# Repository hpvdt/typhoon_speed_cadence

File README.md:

# Typhoon Speed and Cadence

This is the amazing repository for the amazing Speed and Cadance team.
This embedded system uses an STM32 and a hall effect setup to accurately calculate the speed of the bike in real time, displaying the information to an OLED
HOE: Oliver Cai, Juston Lo
Lead: Daniel Dot
Members: Luca M, Rena, Noah, Iris

MEMBERS ADD YOUR LAST NAMES PLEASE I DONT KNOW THEM :(

## Hardware Setup

We must all operate on the same main version of KiCad, 9.0.
Ensure you are always working on the project file, never open the files standalone.

## Firmware Setup

### THIS PART IS VERY IMPORTANT PLEASE READ

We must all operate on the same versions, if we do not then stuff will break. We are currently using:
- STM32CubeIDE 2.0.0
- STM32CubeMX 6.16.0

You must download both to program as the IDE is used oto program while the CubeMX is for the .ioc file to configure the board pinout.

When writing code in the main.c, main.h, or any program where code is overwritten from the .ioc save, PLEASE ENSURE YOU ARE WRITING IN A USER CODE BLOCK, or else your code will be removed.

The main code is found in main.c in the src folder, and whenever working on the code always work in the project folder, dont open the file standalone. 
The logic for the code is commented in code, and any changes MUST also be commented for others to work simultaneously on it.

If there are any questions about the project, message me on disc dot2944, or email daniel.dot@mail.utoronto.ca

## Organization

Pretty self-explanitory, put hardware related files into the `hardware` folder, firmware in the `firmware` folder. Other folders can be added as needed: for example a `media` folder is handy for storing pictures related to a project which can be used in documentation.

## Conventions

Partly for consistency, partly for functionality; please follow the following conventions:

- Try to keep folder names to single words and all lowercase
- Use underscores to separate words in names (e.g. `board_rev1`). **DO NOT USE SPACES! ESPECIALLY FOR FOLDERS CONTAINING CODE!** Spaces in file paths may cause issues in compilers and such so best to avoid them entirely.

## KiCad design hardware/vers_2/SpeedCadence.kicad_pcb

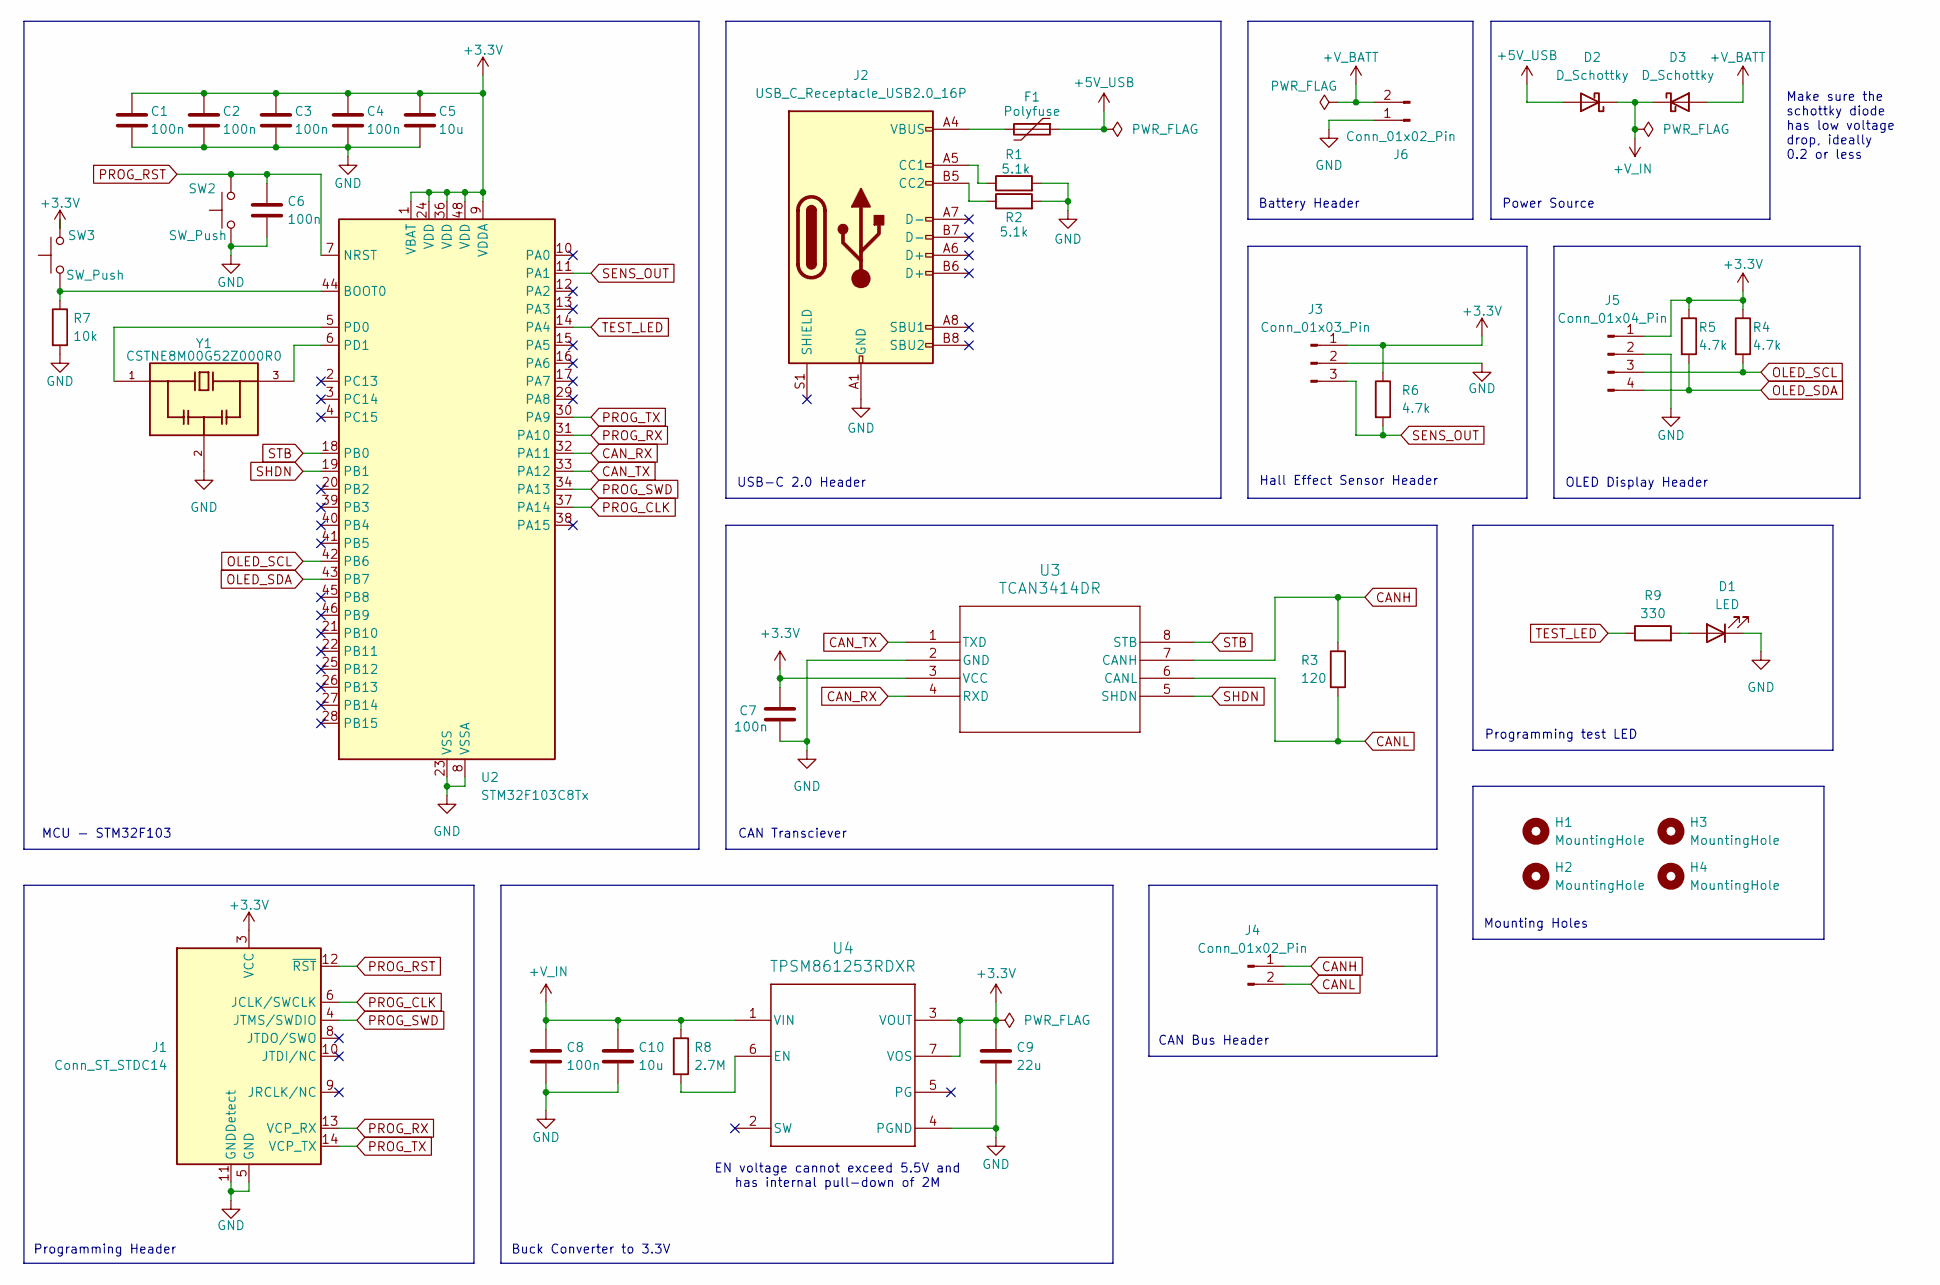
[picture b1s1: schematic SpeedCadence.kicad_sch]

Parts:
C1, C2, C3, C4, C6, C7, C8: 100n; C_0805_2012Metric; Manufacturer Part Number CC0805KRX7R9BB104
C5, C10: 10u; C_0805_2012Metric; Manufacturer Part Number GRM21BR71A106KA73K
C9: 22u; C_0805_2012Metric; Manufacturer Part Number GRM21BZ71A226ME15L
D1: LED; LED_0805_2012Metric; Manufacturer Part Number 5975906507F
D2, D3: D_Schottky; D_SOD-123; Manufacturer Part Number 1N5819HW-7-F
F1: Polyfuse; Fuse_1206_3216Metric; Manufacturer Part Number 0ZCJ0020FF2E
H1, H2, H3, H4: MountingHole; MountingHole_2.2mm_M2
J1: Conn_ST_STDC14; PinHeader_2x07_P1.27mm_Vertical_SMD; Manufacturer Part Number FTSH-107-01-L-DV-K-A
J2: USB_C_Receptacle_USB2.0_16P; USB_C_Receptacle_JAE_DX07S016JA1R1500; Manufacturer Part Number DX07S016JA3R1500
J3: Conn_01x03_Pin; JST_XH_B3B-XH-A_1x03_P2.50mm_Vertical; Manufacturer Part Number B3B-XH-A(LF)(SN)
J4, J6: Conn_01x02_Pin; JST_XH_B2B-XH-A_1x02_P2.50mm_Vertical; Manufacturer Part Number B2B-XH-A-BK(LF)(SN)
J5: Conn_01x04_Pin; JST_XH_B4B-XH-A_1x04_P2.50mm_Vertical; Manufacturer Part Number B4B-XH-A(LF)(SN)
R1, R2: 5.1k; R_0805_2012Metric; Manufacturer Part Number RC0805JR-075K1L
R3: 120; R_0805_2012Metric; Manufacturer Part Number P0603Y60R0BBT
R4, R5, R6: 4.7k; R_0805_2012Metric
R7: 10k; R_0805_2012Metric
R8: 2.7M; R_0805_2012Metric
R9: 330; R_0805_2012Metric
SW2, SW3: SW_Push; SW_SPST_SKQG_WithStem
U2: STM32F103C8Tx; LQFP-48_7x7mm_P0.5mm
U3: TCAN3414DR; SOIC-8_3.9x4.9mm_P1.27mm
U4: TPSM861253RDXR; VREG_TPSM861253RDXR
Y1: CSTNE8M00G52Z000R0; OSC_CSTNE8M00G52Z000R0; PARTREV JGC42-8858A

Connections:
+3.3V: C1.2, C2.2, C3.2, C4.2, C5.1, C7.1, C9.1, J1.3 (VCC), J3.1, J5.1, R4.1, R5.1, R6.1, SW3.2, U2.1 (VBAT), U2.9 (VDDA), U2.24 (VDD), U2.36 (VDD), U2.48 (VDD), U3.3 (VCC), U4.3 (VOUT), U4.7 (VOS), U4.14, U4.15, U4.16, U4.17, U4.18, U4.19
+5V_USB: D2.2 (A), F1.1
+V_BATT: D3.2 (A), J6.2
+V_IN: C8.1, C10.1, D2.1 (K), D3.1 (K), R8.1, U4.1 (VIN)
CANH: J4.1, R3.1, U3.7 (CANH)
CANL: J4.2, R3.2, U3.6 (CANL)
CAN_RX: U2.32 (PA11), U3.4 (RXD)
CAN_TX: U2.33 (PA12), U3.1 (TXD)
GND: C1.1, C2.1, C3.1, C4.1, C5.2, C6.2, C7.2, C8.2, C9.2, C10.2, D1.1 (K), J1.5 (GND), J1.7 (GND), J1.11 (GNDDetect), J2.A1 (GND), J2.A12 (GND), J2.B1 (GND), J2.B12 (GND), J3.2, J5.2, J6.1, R1.2, R2.2, R7.2, SW2.1, U2.8 (VSSA), U2.23 (VSS), U2.35 (VSS), U2.47 (VSS), U3.2 (GND), U4.4 (PGND), Y1.2
unnamed: D1.2 (A), R9.2
unnamed: F1.2, J2.A4 (VBUS), J2.A9 (VBUS), J2.B4 (VBUS), J2.B9 (VBUS)
unnamed: J2.A5 (CC1), R1.1
unnamed: J2.B5 (CC2), R2.1
unnamed: R7.1, SW3.1, U2.44 (BOOT0)
unnamed: U2.5 (PD0), Y1.1
unnamed: U2.6 (PD1), Y1.3
unnamed: R8.2, U4.6 (EN)
OLED_SCL: J5.3, R4.2, U2.42 (PB6)
OLED_SDA: J5.4, R5.2, U2.43 (PB7)
PROG_CLK: J1.6 (JCLK/SWCLK), U2.37 (PA14)
PROG_RST: C6.1, J1.12 (~RST), SW2.2, U2.7 (NRST)
PROG_RX: J1.13 (VCP_RX), U2.31 (PA10)
PROG_SWD: J1.4 (JTMS/SWDIO), U2.34 (PA13)
PROG_TX: J1.14 (VCP_TX), U2.30 (PA9)
SENS_OUT: J3.3, R6.2, U2.11 (PA1)
SHDN: U2.19 (PB1), U3.5 (SHDN)
STB: U2.18 (PB0), U3.8 (STB)
TEST_LED: R9.1, U2.14 (PA4)

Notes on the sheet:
Mounting Holes
CAN Transciever
MCU - STM32F103
CAN Bus Header
Battery Header
USB-C 2.0 Header
Buck Converter to 3.3V
Power Source
Hall Effect Sensor Header
EN voltage cannot exceed 5.5V and has internal pull-down of 2M
OLED Display Header
Programming Header
Programming test LED
Make sure the schottky diode has low voltage drop, ideally 0.2 or less

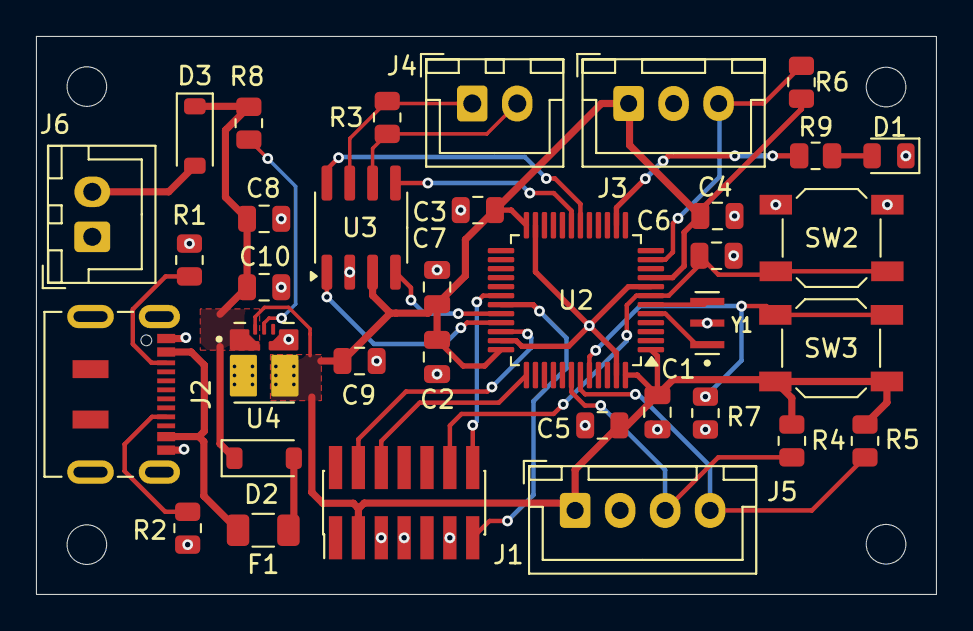
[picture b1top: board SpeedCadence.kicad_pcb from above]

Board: 2 copper layers, 50.0 x 31.0 mm, 39 parts (0 on the bottom side), 28 nets.

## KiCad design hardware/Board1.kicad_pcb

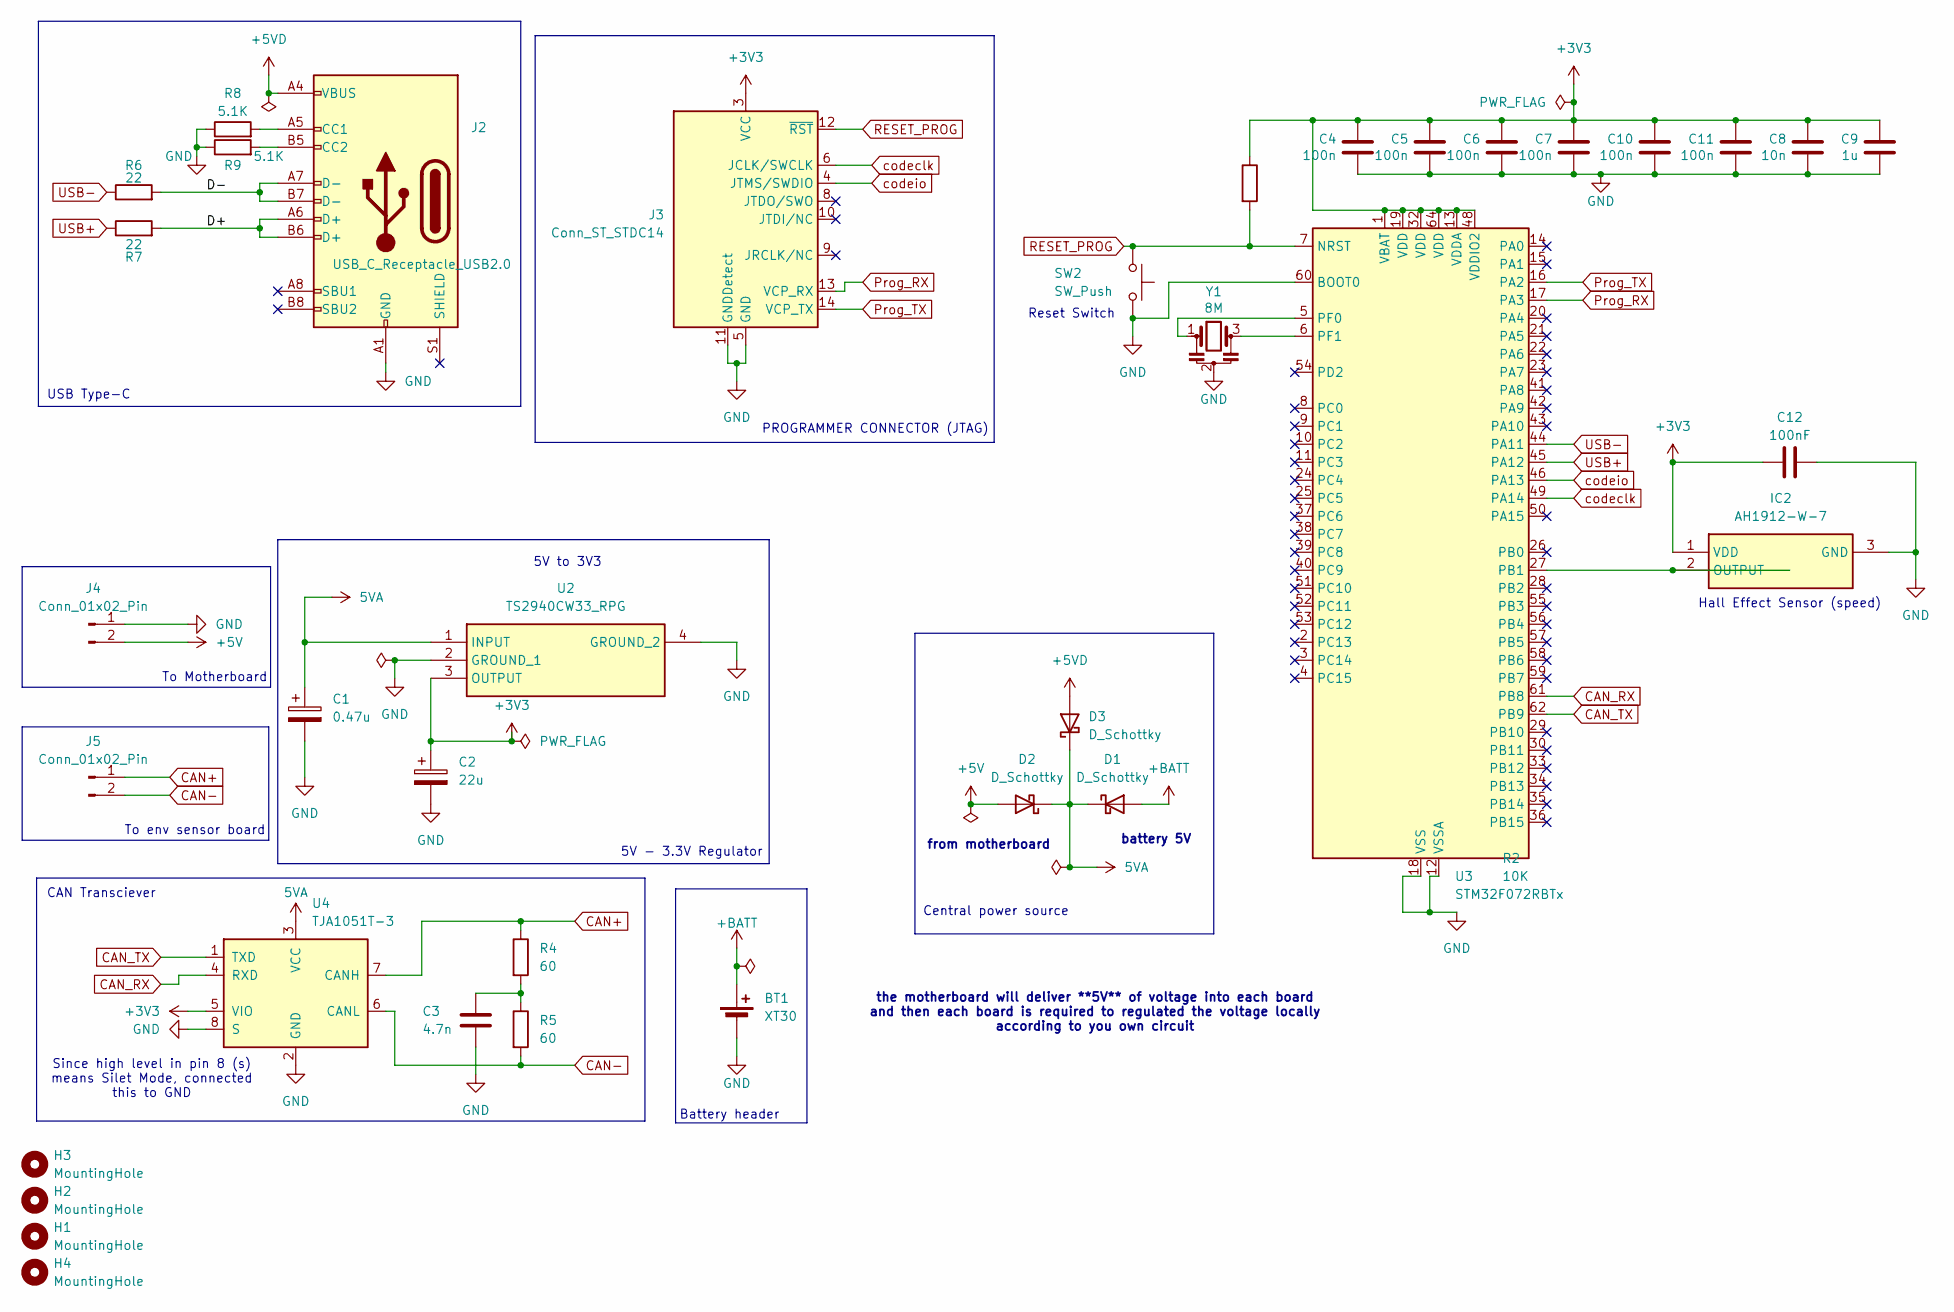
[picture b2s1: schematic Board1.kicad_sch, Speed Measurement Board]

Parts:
BT1: XT30; AMASS_XT30PW-M_1x02_P2.50mm_Horizontal
C1: 0.47u; C_1206_3216Metric
C2: 22u; C_1206_3216Metric
C3: 4.7n; C_0603_1608Metric
C4, C5, C6, C7, C10, C11: 100n; C_0603_1608Metric
C8: 10n; C_0603_1608Metric
C9: 1u; C_0603_1608Metric
C12: 100nF; C_0603_1608Metric
D1, D2, D3: D_Schottky; D_SOD-123
H1, H2, H3, H4: MountingHole; MountingHole_3.2mm_M3_ISO14580
IC2: AH1912-W-7; SC-59; Mouser Part Number 621-AH1912-W-7
J2: USB_C_Receptacle_USB2.0; USB_C_Receptacle_HRO_TYPE-C-31-M-12
J3: Conn_ST_STDC14; PinHeader_2x07_P1.27mm_Vertical_SMD
J4, J5: Conn_01x02_Pin; JST_EH_S2B-EH_1x02_P2.50mm_Horizontal
R2: 10K; R_0603_1608Metric
R4, R5: 60; R_0603_1608Metric
R6, R7: 22; R_0603_1608Metric
R8, R9: 5.1K; R_0603_1608Metric
SW2: SW_Push; SW_SPST_SKQG_WithStem
U2: TS2940CW33_RPG; SOT-223-3_TabPin2; Mouser Part Number 821-TS2940CW33RPG
U3: STM32F072RBTx; LQFP-64_10x10mm_P0.5mm
U4: TJA1051T-3; SOIC-8_3.9x4.9mm_P1.27mm
Y1: 8M; Resonator_SMD_Murata_CSTxExxV-3Pin_3.0x1.1mm

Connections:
5VA: C1.1, D1.1 (K), D2.1 (K), D3.1 (K), U2.1 (INPUT), U4.3 (VCC)
+3V3: C2.1, C4.2, C5.2, C6.2, C7.2, C8.2, C9.2, C10.2, C11.2, C12.1, IC2.1 (VDD), J3.3 (VCC), R2.1, U2.3 (OUTPUT), U3.1 (VBAT), U3.13 (VDDA), U3.19 (VDD), U3.32 (VDD), U3.48 (VDDIO2), U3.64 (VDD), U4.5 (VIO)
+5V: D2.2 (A), J4.2
+5VD: D3.2 (A), J2.A4 (VBUS), J2.A9 (VBUS), J2.B4 (VBUS), J2.B9 (VBUS)
+BATT: BT1.1 (+), D1.2 (A)
/D+: J2.A6 (D+), J2.B6 (D+), R7.2
/D-: J2.A7 (D-), J2.B7 (D-), R6.2
CAN+: J5.1, R4.1, U4.7 (CANH)
CAN-: J5.2, R5.2, U4.6 (CANL)
CAN_RX: U3.61 (PB8), U4.4 (RXD)
CAN_TX: U3.62 (PB9), U4.1 (TXD)
GND: BT1.2 (-), C1.2, C2.2, C3.2, C4.1, C5.1, C6.1, C7.1, C8.1, C9.1, C10.1, C11.1, C12.2, IC2.3 (GND), J2.A1 (GND), J2.A12 (GND), J2.B1 (GND), J2.B12 (GND), J3.5 (GND), J3.7 (GND), J3.11 (GNDDetect), J4.1, R8.1, R9.1, SW2.2, U2.2 (GROUND_1), U2.4 (GROUND_2), U3.12 (VSSA), U3.18 (VSS), U3.31 (VSS), U3.47 (VSS), U3.60 (BOOT0), U3.63 (VSS), U4.2 (GND), U4.8 (S), Y1.2; also elsewhere on the board
unnamed: C3.1, R4.2, R5.1
unnamed: IC2.2 (OUTPUT), U3.27 (PB1)
unnamed: J2.A5 (CC1), R8.2
unnamed: J2.B5 (CC2), R9.2
unnamed: U3.5 (PF0), Y1.1
unnamed: U3.6 (PF1), Y1.3
Prog_RX: J3.13 (VCP_RX), U3.17 (PA3)
Prog_TX: J3.14 (VCP_TX), U3.16 (PA2)
RESET_PROG: J3.12 (~RST), R2.2, SW2.1, U3.7 (NRST)
USB+: R7.1, U3.45 (PA12)
USB-: R6.1, U3.44 (PA11)
codeclk: J3.6 (JCLK/SWCLK), U3.49 (PA14)
codeio: J3.4 (JTMS/SWDIO), U3.46 (PA13)

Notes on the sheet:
To Motherboard
Reset Switch
PROGRAMMER CONNECTOR (JTAG)
Battery header
USB Type-C
5V to 3V3
Central power source
battery 5V
CAN Transciever
the motherboard will deliver **5V** of voltage into each board and then each board is required to regulated the voltage locally according to you own circuit
from motherboard
Hall Effect Sensor (speed)
Since high level in pin 8 (s) means Silet Mode, connected this to GND
To env sensor board
5V - 3.3V Regulator

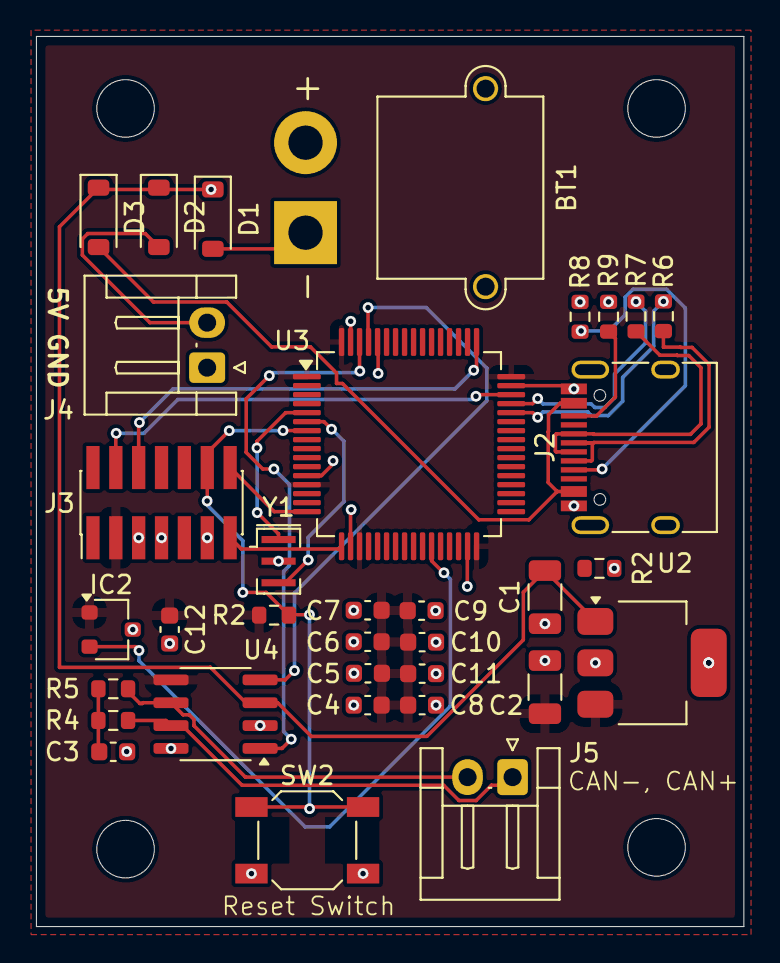
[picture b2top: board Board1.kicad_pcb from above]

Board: 2 copper layers, 39.3 x 49.4 mm, 38 parts (0 on the bottom side), 25 nets.

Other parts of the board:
R2#2: 5.1k; R_0603_1608Metric

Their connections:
GND: R2#2.2; also elsewhere on the board

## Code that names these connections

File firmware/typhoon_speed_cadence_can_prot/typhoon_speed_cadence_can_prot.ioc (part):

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Mcu.Name=STM32F103C(8-B)Tx
Mcu.Package=LQFP48
Mcu.UserName=STM32F103C8Tx
PA10.Mode=Asynchronous
PA10.Signal=USART1_RX
PA11.Mode=CAN_Activate
PA11.Signal=CAN_RX
PA12.Mode=CAN_Activate
PA12.Signal=CAN_TX
PA13.Mode=Serial_Wire
PA13.Signal=SYS_JTMS-SWDIO
PA14.Mode=Serial_Wire
PA14.Signal=SYS_JTCK-SWCLK
PA4.GPIOParameters=GPIO_Label
PA4.GPIO_Label=USR_LED
PA4.Signal=GPIO_Output
PA8.GPIOParameters=GPIO_ModeDefaultEXTI
PA8.GPIO_ModeDefaultEXTI=GPIO_MODE_IT_FALLING
PA8.Signal=GPXTI8
PA9.Mode=Asynchronous
PA9.Signal=USART1_TX
PB6.Mode=I2C
PB6.Signal=I2C1_SCL
PB7.Mode=I2C
PB7.Signal=I2C1_SDA
PD0-OSC_IN.Mode=HSE-External-Oscillator
PD0-OSC_IN.Signal=RCC_OSC_IN
PD1-OSC_OUT.Mode=HSE-External-Oscillator
PD1-OSC_OUT.Signal=RCC_OSC_OUT
RCC.SYSCLKFreq_VALUE=32000000
RCC.SYSCLKSource=RCC_SYSCLKSOURCE_PLLCLK
board=custom

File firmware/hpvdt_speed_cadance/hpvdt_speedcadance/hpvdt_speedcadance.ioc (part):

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Mcu.Name=STM32F103C(8-B)Tx
Mcu.Package=LQFP48
Mcu.UserName=STM32F103C8Tx
PA1.GPIOParameters=GPIO_PuPd,GPIO_Label,GPIO_ModeDefaultEXTI
PA1.GPIO_Label=HALLEFFECT_PIN
PA1.GPIO_ModeDefaultEXTI=GPIO_MODE_IT_FALLING
PA1.GPIO_PuPd=GPIO_PULLUP
PA1.Signal=GPXTI1
PA4.GPIOParameters=GPIO_Label
PA4.GPIO_Label=LED
PA4.Signal=GPIO_Output
PB6.GPIOParameters=GPIO_Label
PB6.GPIO_Label=OLED_SCL
PB6.Mode=I2C
PB6.Signal=I2C1_SCL
PB7.GPIOParameters=GPIO_Label
PB7.GPIO_Label=OLED_SDA
PB7.Mode=I2C
PB7.Signal=I2C1_SDA
PD0-OSC_IN.GPIOParameters=GPIO_Label
PD0-OSC_IN.GPIO_Label=RESONATOR_IN
PD0-OSC_IN.Mode=HSE-External-Oscillator
PD0-OSC_IN.Signal=RCC_OSC_IN
PD1-OSC_OUT.GPIOParameters=GPIO_Label
PD1-OSC_OUT.GPIO_Label=RESONATOR_OUT
PD1-OSC_OUT.Mode=HSE-External-Oscillator
PD1-OSC_OUT.Signal=RCC_OSC_OUT
RCC.SYSCLKFreq_VALUE=32000000
RCC.SYSCLKSource=RCC_SYSCLKSOURCE_PLLCLK
board=custom

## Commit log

2024-07-12 copied everything from old repo
2024-10-14 Updated with comments
2024-10-18 Updated differential pair fill zone
2024-10-18 Comments Added
2024-10-31 Modified Schematic according to comments/meeting
2024-10-31 Updated board schematic with comments
2024-11-15 Made a few changes regarding STM32
2024-11-16 added order details (not finalised)
2024-11-17 final revision of the speed and cadence board
    Finished re routing the PCB and also did BOM and production needed for JLC PCB
2024-11-17 Final small changes, only silkscreen stuff
2025-07-07 Added version 2
2025-07-07 Revision 2
2025-07-08 Updated LDO
2025-07-08 PCB design complete
2025-07-08 Small adjustment
2025-07-10 Comments for vers2
2025-07-10 Fixed minor changes
2025-07-11 removed tvs diode
2025-07-11 R3, R4 changed to 0603 footprint
2025-07-20 Changed to 6.4V with buck converter
2025-07-21 minor changes
2025-07-25 test LED and USB footprint change
2025-07-29 Changed termination on CAN lines from 60 ohm to 120 ohm
2025-07-29 Added manufacturers and manufacturer part numbers
2025-07-29 Small change to labels
2026-01-09 Added Firmware
2026-02-04 Added Blinky Code
    Found out there was a bug regarding programming the project. Just started a new one isntead
2026-02-10 Added CAN prototype code (did not work)
2026-03-02 Changed Clock Config and Switched to Interrupt Driven Logic
    Justin Lo (STD) I changed your clock config as well to work with the external 32MHz so for your CAN and UART consider this
2026-03-02 Im an idiot and dont know how git works, this is the real commit
2026-03-11 Finished Firmware for the Board
    - Capable of accurate speeds up to 1600 rpm (approx 200km/h relative to the bike)
    - Final implementation on the bike is required
